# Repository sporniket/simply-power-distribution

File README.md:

# Simply power distribution by Sporniket

> [WARNING] Please read carefully this note before using this project. It contains important facts.

Content

1. What is **Simply power distribution by Sporniket**, and when to use it ?
2. What should you know before using **Simply power distribution by Sporniket** ?
3. How to use **Simply power distribution by Sporniket** ?
4. Known issues
5. Miscellanous

## 1. What is **Simply power distribution by Sporniket**, and when to use it ?

**Simply power distribution by Sporniket** is a small PCB that holds a 55/21 barrel jack connector, a power switch, and two rails of pin headers (positive and ground), for distributing power to multiple boards, or powering a breadboard-type prototyping board.

### Licence

**Simply power distribution by Sporniket** is published under the Creative Commons CC0 license. You can find a copy of the licence there : https://creativecommons.org/publicdomain/zero/1.0/legalcode

You can copy, modify, distribute and perform the work, even for commercial purposes, all without asking permission.

**Simply power distribution by Sporniket** is distributed in the hope that it will be useful, but WITHOUT ANY WARRANTY; without even the implied warranty of MERCHANTABILITY or FITNESS FOR A PARTICULAR PURPOSE.

### Release notes

> No releases yet

## 2. What should you know before using **Simply power distribution by Sporniket** ?

**Simply power distribution by Sporniket** is made using Kicad 7.

> Do not use **Simply power distribution by Sporniket** if this project is not suitable for your project.

## 3. How to use **Simply power distribution by Sporniket** ?

### From sources

To get the latest available work, one must clone the git repository and its submodules.

	git clone --recurse-submodules https://github.com/sporniket/simply-power-distribution.git

Then, open the project with Kicad 7.

## 4. Known issues
See the [project issues](https://github.com/sporniket/simply-power-distribution/issues) page.

## 5. Miscellanous

### Report issues
Use the [project issues](https://github.com/sporniket/simply-power-distribution/issues) page.

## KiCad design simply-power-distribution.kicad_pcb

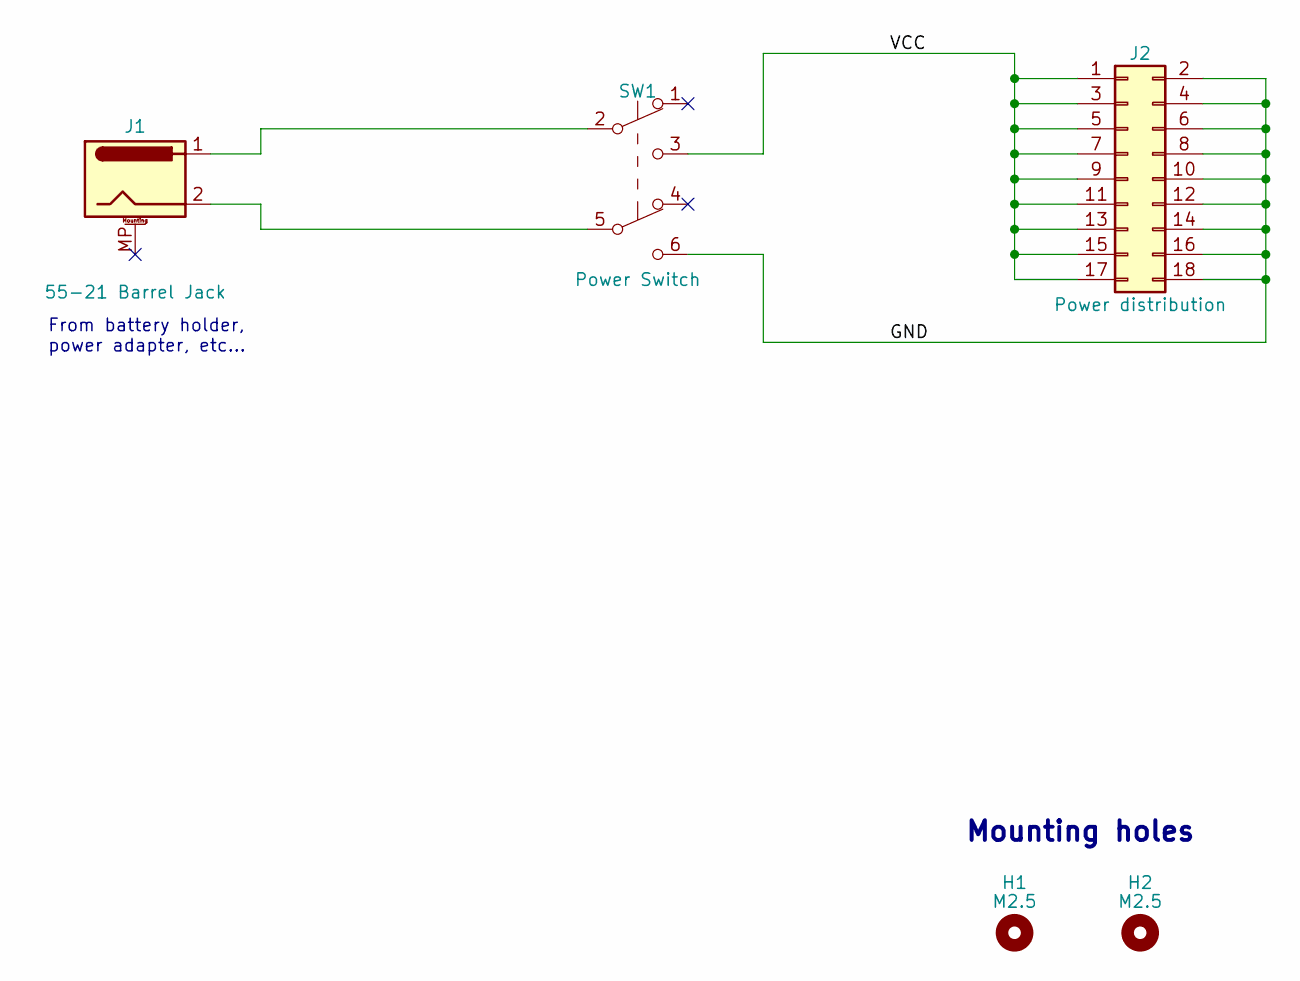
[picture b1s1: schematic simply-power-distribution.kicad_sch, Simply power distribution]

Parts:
H1, H2: M2.5; MountingHole_2.7mm_M2.5
J1: 55-21 Barrel Jack; BarrelJack_Horizontal
J2: Power distribution; PinSocket_2x09_P2.54mm_Vertical
SW1: Power Switch; g-switch_22f12-gxxx

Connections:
/GND: J2.2, J2.4, J2.6, J2.8, J2.10, J2.12, J2.14, J2.16, J2.18, SW1.6 (C)
/VCC: J2.1, J2.3, J2.5, J2.7, J2.9, J2.11, J2.13, J2.15, J2.17, SW1.3 (C)
unnamed: J1.1, SW1.2 (B)
unnamed: J1.2, SW1.5 (B)

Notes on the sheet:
Mounting holes
From battery holder, power adapter, etc...

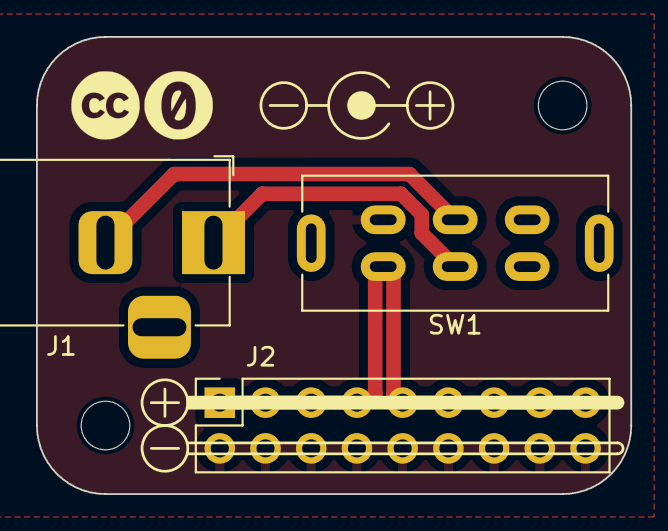
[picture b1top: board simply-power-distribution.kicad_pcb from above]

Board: 2 copper layers, 33.0 x 25.4 mm, 5 parts (0 on the bottom side), 4 nets.

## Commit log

2023-12-20 init kicad project
2023-12-20 init README
2023-12-20 fixes README cloning instructions
2023-12-20 done schematic
2023-12-20 pcb -- layout
2023-12-20 pcb -- traces and markings
2024-01-21 Prepare RC1
2024-01-21 RC1 is ready
